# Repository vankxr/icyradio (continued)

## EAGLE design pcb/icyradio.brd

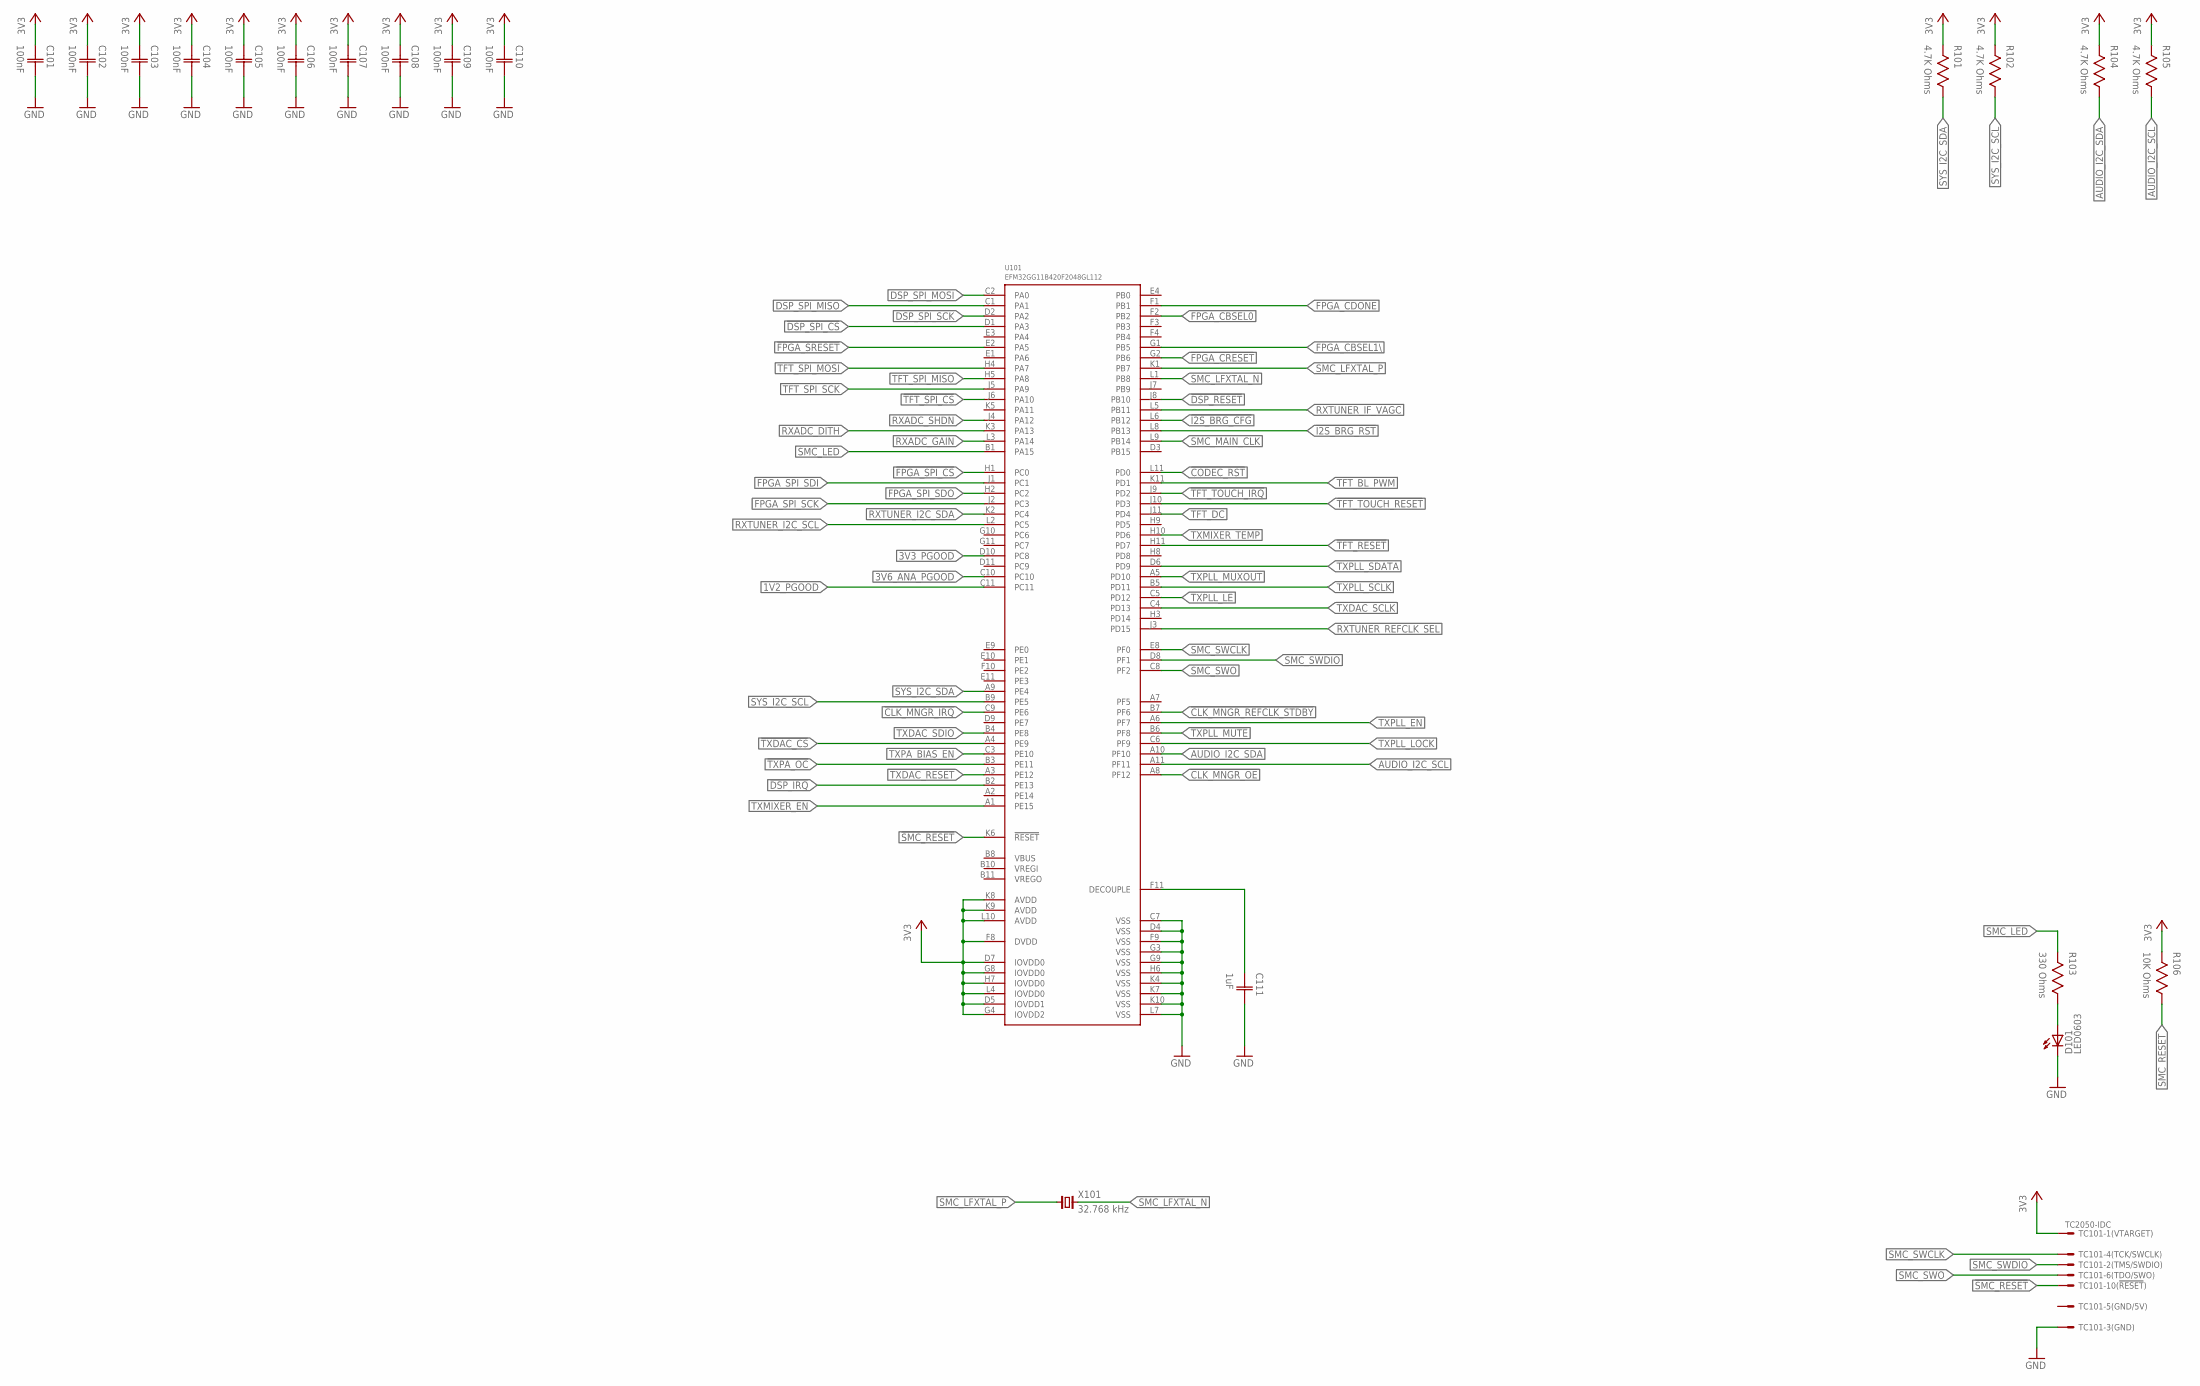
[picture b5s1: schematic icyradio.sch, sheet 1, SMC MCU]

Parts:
C101, C102, C103, C104, C105, C106, C107, C108, C109, C110: 100nF; CAP0603
C111: 1uF; CAP0603
D101: LED0603; 0603
R101, R102, R104, R105: 4.7K Ohms; RES0603
R103: 330 Ohms; RES0603
R106: 10K Ohms; RES0603
TC101: TC2050-IDC
U101: EFM32GG11B420F2048GL112; BGA112
X101: 32.768 kHz; 2-SMD-3215

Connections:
1V2_PGOOD: U101.C11; also elsewhere on the board
3V3: C101.1 (C1), C102.1 (C1), C103.1 (C1), C104.1 (C1), C105.1 (C1), C106.1 (C1), C107.1 (C1), C108.1 (C1), C109.1 (C1), C110.1 (C1), R101.2, R102.2, R104.2, R105.2, R106.2, TC101.1, U101.D5 (IOVDD1), U101.D7 (IOVDD0), U101.F8 (DVDD), U101.G4 (IOVDD2), U101.G8 (IOVDD0), U101.H7 (IOVDD0), U101.K8 (AVDD), U101.K9 (AVDD), U101.L4 (IOVDD0), U101.L10 (AVDD); also elsewhere on the board
3V3_PGOOD: U101.D10 (PC8); also elsewhere on the board
3V6_ANA_PGOOD: U101.C10; also elsewhere on the board
!CLK_MNGR_IRQ: U101.C9 (PE6); also elsewhere on the board
!CLK_MNGR_OE: U101.A8 (PF12); also elsewhere on the board
!CLK_MNGR_REFCLK_STDBY: U101.B7 (PF6); also elsewhere on the board
!CODEC_RST: U101.L11 (PD0); also elsewhere on the board
!DSP_IRQ: U101.B2 (PE13); also elsewhere on the board
!DSP_RESET: U101.J8 (PB10); also elsewhere on the board
!DSP_SPI_CS: U101.D1 (PA3); also elsewhere on the board
!FPGA_CRESET: U101.G2 (PB6); also elsewhere on the board
!FPGA_SPI_CS: U101.H1 (PC0); also elsewhere on the board
!FPGA_SRESET: U101.E2 (PA5); also elsewhere on the board
!I2S_BRG_CFG: U101.L6 (PB12); also elsewhere on the board
!I2S_BRG_RST: U101.L8 (PB13); also elsewhere on the board
!SMC_RESET: R106.1, TC101.10, U101.K6 (!RESET)
!TFT_RESET: U101.H11 (PD7); also elsewhere on the board
!TFT_SPI_CS: U101.J6 (PA10); also elsewhere on the board
!TFT_TOUCH_IRQ: U101.J9 (PD2); also elsewhere on the board
!TFT_TOUCH_RESET: U101.J10 (PD3); also elsewhere on the board
!TXDAC_CS: U101.A4 (PE9); also elsewhere on the board
!TXPA_OC: U101.B3 (PE11); also elsewhere on the board
!TXPLL_MUTE: U101.B6 (PF8); also elsewhere on the board
AUDIO_I2C_SCL: R105.1, U101.A11 (PF11); also elsewhere on the board
AUDIO_I2C_SDA: R104.1, U101.A10 (PF10); also elsewhere on the board
DSP_SPI_MISO: U101.C1 (PA1); also elsewhere on the board
DSP_SPI_MOSI: U101.C2 (PA0); also elsewhere on the board
DSP_SPI_SCK: U101.D2 (PA2); also elsewhere on the board
FPGA_CBSEL0: U101.F2 (PB2); also elsewhere on the board
FPGA_CBSEL1\: U101.G1 (PB5); also elsewhere on the board
FPGA_CDONE: U101.F1 (PB1); also elsewhere on the board
FPGA_SPI_SCK: U101.J2 (PC3); also elsewhere on the board
FPGA_SPI_SDI: U101.J1 (PC1); also elsewhere on the board
FPGA_SPI_SDO: U101.H2 (PC2); also elsewhere on the board
GND: C101.2 (C2), C102.2 (C2), C103.2 (C2), C104.2 (C2), C105.2 (C2), C106.2 (C2), C107.2 (C2), C108.2 (C2), C109.2 (C2), C110.2 (C2), C111.2 (C2), D101.1 (C), TC101.3, U101.C7 (VSS), U101.D4 (VSS), U101.F9 (VSS), U101.G3 (VSS), U101.G9 (VSS), U101.H6 (VSS), U101.K4 (VSS), U101.K7 (VSS), U101.K10 (VSS), U101.L7 (VSS); also elsewhere on the board
unnamed: D101.2 (A), R103.1
RXADC_DITH: U101.K3 (PA13); also elsewhere on the board
RXADC_GAIN: U101.L3 (PA14); also elsewhere on the board
RXADC_SHDN: U101.J4 (PA12); also elsewhere on the board
RXTUNER_I2C_SCL: U101.L2 (PC5); also elsewhere on the board
RXTUNER_I2C_SDA: U101.K2 (PC4); also elsewhere on the board
RXTUNER_IF_VAGC: U101.L5 (PB11); also elsewhere on the board
RXTUNER_REFCLK_SEL: U101.J3 (PD15); also elsewhere on the board
SMC_LED: R103.2, U101.B1 (PA15)
SMC_LFXTAL_N: U101.L1 (PB8), X101.2
SMC_LFXTAL_P: U101.K1 (PB7), X101.1
SMC_MAIN_CLK: U101.L9 (PB14); also elsewhere on the board
SMC_SWCLK: TC101.4, U101.E8 (PF0)
SMC_SWDIO: TC101.2, U101.D8 (PF1)
SMC_SWO: TC101.6, U101.C8 (PF2)
SMC_VCORE: C111.1 (C1), U101.F11 (DECOUPLE)
SYS_I2C_SCL: R102.1, U101.B9 (PE5); also elsewhere on the board
SYS_I2C_SDA: R101.1, U101.A9 (PE4); also elsewhere on the board
TFT_BL_PWM: U101.K11 (PD1); also elsewhere on the board
TFT_DC: U101.J11 (PD4); also elsewhere on the board
TFT_SPI_MISO: U101.H5 (PA8); also elsewhere on the board
TFT_SPI_MOSI: U101.H4 (PA7); also elsewhere on the board
TFT_SPI_SCK: U101.J5 (PA9); also elsewhere on the board
TXDAC_RESET: U101.A3 (PE12); also elsewhere on the board
TXDAC_SCLK: U101.C4 (PD13); also elsewhere on the board
TXDAC_SDIO: U101.B4 (PE8); also elsewhere on the board
TXMIXER_EN: U101.A1 (PE15); also elsewhere on the board
TXMIXER_TEMP: U101.H10 (PD6); also elsewhere on the board
TXPA_BIAS_EN: U101.C3 (PE10); also elsewhere on the board
TXPLL_EN: U101.A6 (PF7); also elsewhere on the board
TXPLL_LE: U101.C5 (PD12); also elsewhere on the board
TXPLL_LOCK: U101.C6 (PF9); also elsewhere on the board
TXPLL_MUXOUT: U101.A5 (PD10); also elsewhere on the board
TXPLL_SCLK: U101.B5 (PD11); also elsewhere on the board
TXPLL_SDATA: U101.D6 (PD9); also elsewhere on the board

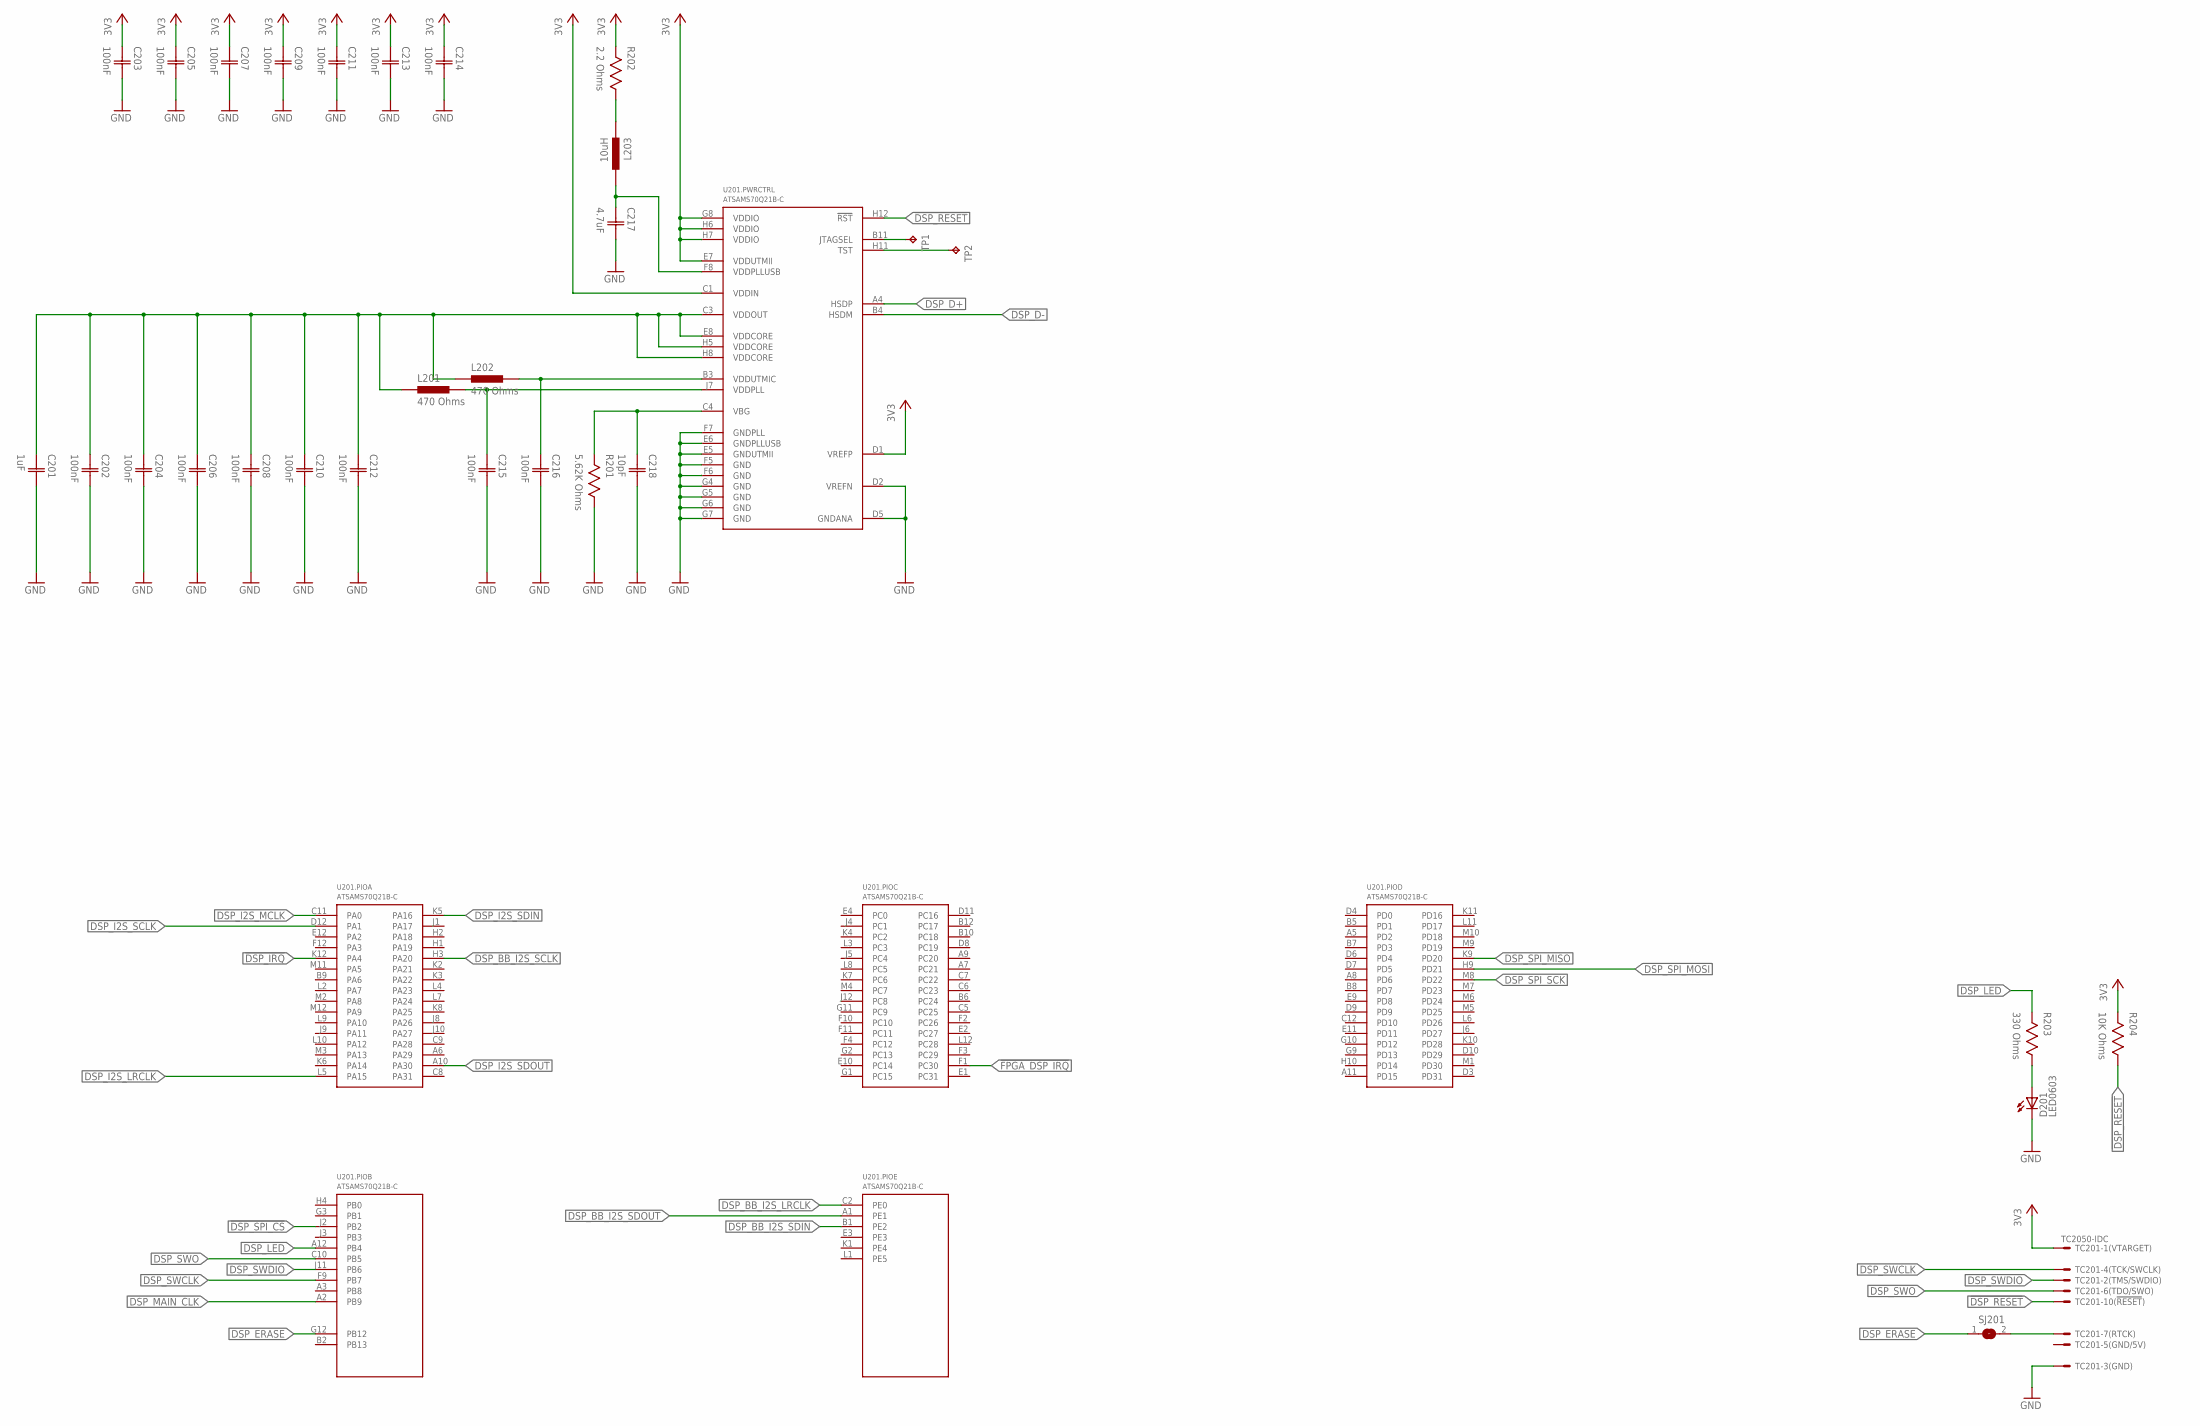
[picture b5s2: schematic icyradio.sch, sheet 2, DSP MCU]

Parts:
C201: 1uF; CAP0603
C202, C203, C204, C205, C206, C207, C208, C209, C210, C211, C212, C213, C214, C215, C216: 100nF; CAP0603
C217: 4.7uF; CAP0603
C218: 10pF; CAP0603
D201: LED0603; 0603
L201, L202: 470 Ohms; IND0603
L203: 10uH; IND0603
R201: 5.62K Ohms; RES0603
R202: 2.2 Ohms; RES0603
R203: 330 Ohms; RES0603
R204: 10K Ohms; RES0603
SJ201: SJS; SJ_S
TC201: TC2050-IDC
TP1, TP2: TESTPOINT-0.7MM; PAD0.7MM
U201: ATSAMS70Q21B-C; LFBGA144

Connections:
3V3: C203.1 (C1), C205.1 (C1), C207.1 (C1), C209.1 (C1), C211.1 (C1), C213.1 (C1), C214.1 (C1), R202.2, R204.2, TC201.1, U201.C1 (VDDIN), U201.D1 (VREFP), U201.E7 (VDDUTMII), U201.G8 (VDDIO), U201.H6 (VDDIO), U201.H7 (VDDIO); also elsewhere on the board
!DSP_IRQ: U201.K12 (PA4); also elsewhere on the board
!DSP_RESET: R204.1, TC201.10, U201.H12 (!RST); also elsewhere on the board
!DSP_SPI_CS: U201.J2 (PB2); also elsewhere on the board
!FPGA_DSP_IRQ: U201.F1 (PC30); also elsewhere on the board
DSP_BB_I2S_LRCLK: U201.C2 (PE0); also elsewhere on the board
DSP_BB_I2S_SCLK: U201.H3 (PA20); also elsewhere on the board
DSP_BB_I2S_SDIN: U201.B1 (PE2); also elsewhere on the board
DSP_BB_I2S_SDOUT: U201.A1 (PE1); also elsewhere on the board
DSP_D+: U201.A4 (HSDP); also elsewhere on the board
DSP_D-: U201.B4 (HSDM); also elsewhere on the board
DSP_ERASE: SJ201.1, U201.G12 (PB12)
DSP_I2S_LRCLK: U201.L5 (PA15); also elsewhere on the board
DSP_I2S_MCLK: U201.C11 (PA0); also elsewhere on the board
DSP_I2S_SCLK: U201.D12 (PA1); also elsewhere on the board
DSP_I2S_SDIN: U201.K5 (PA16); also elsewhere on the board
DSP_I2S_SDOUT: U201.A10 (PA30); also elsewhere on the board
DSP_JTAGSEL: TP1.TP, U201.B11 (JTAGSEL)
DSP_LED: R203.2, U201.A12 (PB4)
DSP_MAIN_CLK: U201.A2 (PB9); also elsewhere on the board
DSP_SPI_MISO: U201.K9 (PD20); also elsewhere on the board
DSP_SPI_MOSI: U201.H9 (PD21); also elsewhere on the board
DSP_SPI_SCK: U201.M8 (PD22); also elsewhere on the board
DSP_SWCLK: TC201.4, U201.F9 (PB7)
DSP_SWDIO: TC201.2, U201.J11 (PB6)
DSP_SWO: TC201.6, U201.C10 (PB5)
DSP_TST: TP2.TP, U201.H11 (TST)
DSP_VDDOUT: C201.1 (C1), C202.1 (C1), C204.1 (C1), C206.1 (C1), C208.1 (C1), C210.1 (C1), C212.1 (C1), L201.1, L202.1, U201.C3 (VDDOUT), U201.E8 (VDDCORE), U201.H5 (VDDCORE), U201.H8 (VDDCORE)
DSP_VDDPLLUSB: C217.1 (C1), L203.2, U201.F8 (VDDPLLUSB)
GND: C201.2 (C2), C202.2 (C2), C203.2 (C2), C204.2 (C2), C205.2 (C2), C206.2 (C2), C207.2 (C2), C208.2 (C2), C209.2 (C2), C210.2 (C2), C211.2 (C2), C212.2 (C2), C213.2 (C2), C214.2 (C2), C215.2 (C2), C216.2 (C2), C217.2 (C2), C218.2 (C2), D201.1 (C), R201.1, TC201.3, U201.D2 (VREFN), U201.D5 (GNDANA), U201.E5 (GNDUTMII), U201.E6 (GNDPLLUSB), U201.F5 (GND), U201.F6 (GND), U201.F7 (GNDPLL), U201.G4 (GND), U201.G5 (GND), U201.G6 (GND), U201.G7 (GND); also elsewhere on the board
unnamed: L203.1, R202.1
unnamed: C218.1 (C1), R201.2, U201.C4 (VBG)
unnamed: C215.1 (C1), L201.2, U201.J7 (VDDPLL)
unnamed: C216.1 (C1), L202.2, U201.B3 (VDDUTMIC)
unnamed: SJ201.2, TC201.7
unnamed: D201.2 (A), R203.1

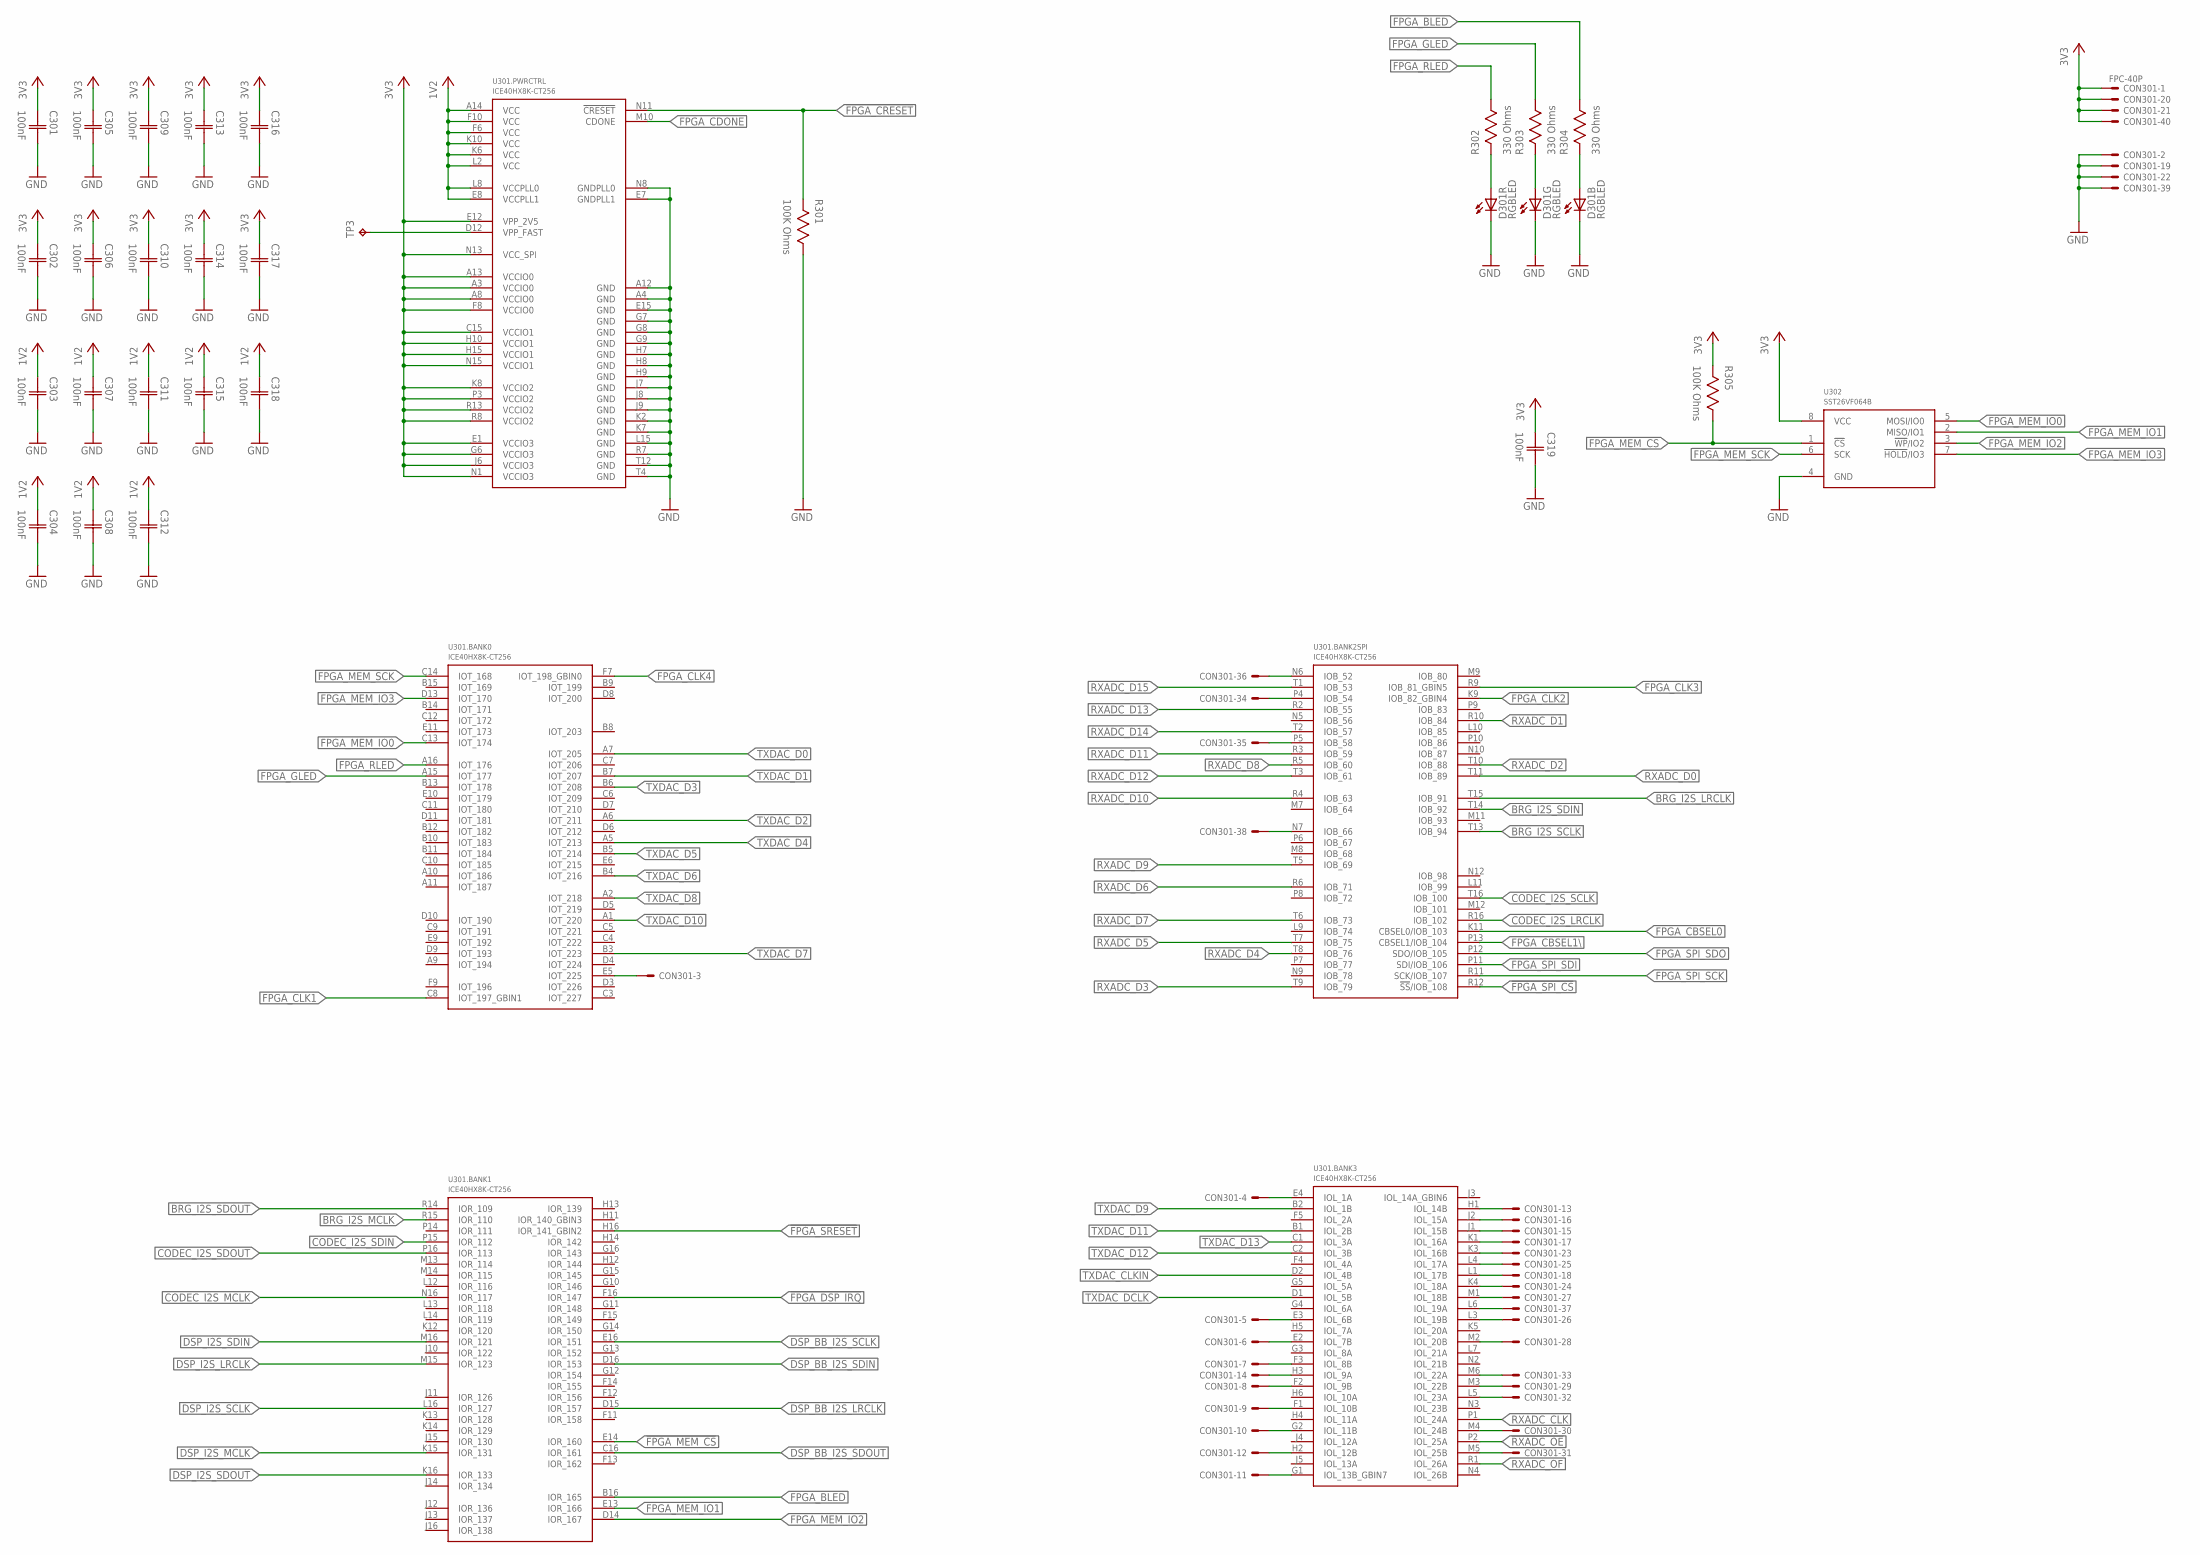
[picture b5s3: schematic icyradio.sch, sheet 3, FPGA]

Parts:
C301, C302, C303, C304, C305, C306, C307, C308, C309, C310, C311, C312, C313, C314, C315, C316, C317, C318, C319: 100nF; CAP0603
CON301: FPC-40P
D301: RGBLED; 5050
R301, R305: 100K Ohms; RES0603
R302, R303, R304: 330 Ohms; RES0603
TP3: TESTPOINT-0.7MM; PAD0.7MM
U301: ICE40HX8K-CT256; CABGA256
U302: SST26VF064B; WSOIC8

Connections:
1V2: C303.1 (C1), C304.1 (C1), C307.1 (C1), C308.1 (C1), C311.1 (C1), C312.1 (C1), C315.1 (C1), C318.1 (C1), U301.A14 (VCC), U301.E8 (VCCPLL1), U301.F6 (VCC), U301.F10 (VCC), U301.K6 (VCC), U301.K10 (VCC), U301.L2 (VCC), U301.L8 (VCCPLL0); also elsewhere on the board
3V3: C301.1 (C1), C302.1 (C1), C305.1 (C1), C306.1 (C1), C309.1 (C1), C310.1 (C1), C313.1 (C1), C314.1 (C1), C316.1 (C1), C317.1 (C1), C319.1 (C1), CON301.1, CON301.20, CON301.21, CON301.40, R305.2, U301.A3 (VCCIO0), U301.A8 (VCCIO0), U301.A13 (VCCIO0), U301.C15 (VCCIO1), U301.E1 (VCCIO3), U301.E12 (VPP_2V5), U301.F8 (VCCIO0), U301.G6 (VCCIO3), U301.H10 (VCCIO1), U301.H15 (VCCIO1), U301.J6 (VCCIO3), U301.K8 (VCCIO2), U301.N1 (VCCIO3), U301.N13 (VCC_SPI), U301.N15 (VCCIO1), U301.P3 (VCCIO2), U301.R8 (VCCIO2), U301.R13 (VCCIO2), U302.8 (VCC); also elsewhere on the board
!FPGA_CRESET: R301.2, U301.N11 (!CRESET); also elsewhere on the board
!FPGA_DSP_IRQ: U301.F16 (IOR_147); also elsewhere on the board
!FPGA_MEM_CS: R305.1, U301.E14 (IOR_160), U302.1 (!CS!)
!FPGA_SPI_CS: U301.R12 (!SS!/IOB_108); also elsewhere on the board
!FPGA_SRESET: U301.H16 (IOR_141_GBIN2); also elsewhere on the board
!RXADC_OE: U301.P2 (IOL_25A); also elsewhere on the board
BRG_I2S_LRCLK: U301.T15 (IOB_91); also elsewhere on the board
BRG_I2S_MCLK: U301.R15 (IOR_110); also elsewhere on the board
BRG_I2S_SCLK: U301.T13 (IOB_94); also elsewhere on the board
BRG_I2S_SDIN: U301.T14 (IOB_92); also elsewhere on the board
BRG_I2S_SDOUT: U301.R14 (IOR_109); also elsewhere on the board
CODEC_I2S_LRCLK: U301.R16 (IOB_102); also elsewhere on the board
CODEC_I2S_MCLK: U301.N16 (IOR_117); also elsewhere on the board
CODEC_I2S_SCLK: U301.T16 (IOB_100); also elsewhere on the board
CODEC_I2S_SDIN: U301.P15 (IOR_112); also elsewhere on the board
CODEC_I2S_SDOUT: U301.P16 (IOR_113); also elsewhere on the board
DSP_BB_I2S_LRCLK: U301.D15 (IOR_157); also elsewhere on the board
DSP_BB_I2S_SCLK: U301.E16 (IOR_151); also elsewhere on the board
DSP_BB_I2S_SDIN: U301.D16 (IOR_153); also elsewhere on the board
DSP_BB_I2S_SDOUT: U301.C16 (IOR_161); also elsewhere on the board
DSP_I2S_LRCLK: U301.M15 (IOR_123); also elsewhere on the board
DSP_I2S_MCLK: U301.K15 (IOR_131); also elsewhere on the board
DSP_I2S_SCLK: U301.L16 (IOR_127); also elsewhere on the board
DSP_I2S_SDIN: U301.M16 (IOR_121); also elsewhere on the board
DSP_I2S_SDOUT: U301.K16 (IOR_133); also elsewhere on the board
EXP_IO0: CON301.3, U301.E5 (IOT_225)
EXP_IO1: CON301.4, U301.E4 (IOL_1A)
EXP_IO2: CON301.5, U301.E3 (IOL_6B)
EXP_IO3: CON301.6, U301.E2 (IOL_7B)
EXP_IO4: CON301.7, U301.F3 (IOL_8B)
EXP_IO5: CON301.8, U301.F2 (IOL_9B)
EXP_IO6: CON301.9, U301.F1 (IOL_10B)
EXP_IO7: CON301.10, U301.G2 (IOL_11B)
EXP_IO8: CON301.11, U301.G1 (IOL_13B_GBIN7)
EXP_IO9: CON301.12, U301.H2 (IOL_12B)
EXP_IO10: CON301.13, U301.H1 (IOL_14B)
EXP_IO11: CON301.14, U301.H3 (IOL_9A)
EXP_IO12: CON301.15, U301.J1 (IOL_15B)
EXP_IO13: CON301.16, U301.J2 (IOL_15A)
EXP_IO14: CON301.17, U301.K1 (IOL_16A)
EXP_IO15: CON301.18, U301.L1 (IOL_17B)
EXP_IO16: CON301.23, U301.K3 (IOL_16B)
EXP_IO17: CON301.24, U301.K4 (IOL_18A)
EXP_IO18: CON301.25, U301.L4 (IOL_17A)
EXP_IO19: CON301.26, U301.L3 (IOL_19B)
EXP_IO20: CON301.27, U301.M1 (IOL_18B)
EXP_IO21: CON301.28, U301.M2 (IOL_20B)
EXP_IO22: CON301.29, U301.M3 (IOL_22B)
EXP_IO23: CON301.30, U301.M4 (IOL_24B)
EXP_IO24: CON301.31, U301.M5 (IOL_25B)
EXP_IO25: CON301.32, U301.L5 (IOL_23A)
EXP_IO26: CON301.33, U301.M6 (IOL_22A)
EXP_IO27: CON301.34, U301.P4 (IOB_54)
EXP_IO28: CON301.35, U301.P5 (IOB_58)
EXP_IO29: CON301.36, U301.N6 (IOB_52)
EXP_IO30: CON301.37, U301.L6 (IOL_19A)
EXP_IO31: CON301.38, U301.N7 (IOB_66)
FPGA_BLED: R304.1, U301.B16 (IOR_165)
FPGA_CBSEL0: U301.K11 (CBSEL0/IOB_103); also elsewhere on the board
FPGA_CBSEL1\: U301.P13 (CBSEL1/IOB_104); also elsewhere on the board
FPGA_CDONE: U301.M10 (CDONE); also elsewhere on the board
FPGA_CLK1: U301.C8 (IOT_197_GBIN1); also elsewhere on the board
FPGA_CLK2: U301.K9 (IOB_82_GBIN4); also elsewhere on the board
FPGA_CLK3: U301.R9 (IOB_81_GBIN5); also elsewhere on the board
FPGA_CLK4: U301.F7 (IOT_198_GBIN0); also elsewhere on the board
FPGA_GLED: R303.1, U301.A15 (IOT_177)
FPGA_MEM_IO0: U301.C13 (IOT_174), U302.5 (MOSI/IO0)
FPGA_MEM_IO1: U301.E13 (IOR_166), U302.2 (MISO/IO1)
FPGA_MEM_IO2: U301.D14 (IOR_167), U302.3 (!WP!/IO2)
FPGA_MEM_IO3: U301.D13 (IOT_170), U302.7 (!HOLD!/IO3)
FPGA_MEM_SCK: U301.C14 (IOT_168), U302.6 (SCK)
FPGA_RLED: R302.1, U301.A16 (IOT_176)
FPGA_SPI_SCK: U301.R11 (SCK/IOB_107); also elsewhere on the board
FPGA_SPI_SDI: U301.P11 (SDI/IOB_106); also elsewhere on the board
FPGA_SPI_SDO: U301.P12 (SDO/IOB_105); also elsewhere on the board
FPGA_VPP_FAST: TP3.TP, U301.D12 (VPP_FAST)
GND: C301.2 (C2), C302.2 (C2), C303.2 (C2), C304.2 (C2), C305.2 (C2), C306.2 (C2), C307.2 (C2), C308.2 (C2), C309.2 (C2), C310.2 (C2), C311.2 (C2), C312.2 (C2), C313.2 (C2), C314.2 (C2), C315.2 (C2), C316.2 (C2), C317.2 (C2), C318.2 (C2), C319.2 (C2), CON301.2, CON301.19, CON301.22, CON301.39, D301.4 (C), D301.5 (C), D301.6 (C), R301.1, U301.A4 (GND), U301.A12 (GND), U301.E7 (GNDPLL1), U301.E15 (GND), U301.G7 (GND), U301.G8 (GND), U301.G9 (GND), U301.H7 (GND), U301.H8 (GND), U301.H9 (GND), U301.J7 (GND), U301.J8 (GND), U301.J9 (GND), U301.K2 (GND), U301.K7 (GND), U301.L15 (GND), U301.N8 (GNDPLL0), U301.R7 (GND), U301.T4 (GND), U301.T12 (GND), U302.4 (GND); also elsewhere on the board
unnamed: D301.2 (A), R302.2
unnamed: D301.1 (A), R303.2
unnamed: D301.3 (A), R304.2
RXADC_CLK: U301.P1 (IOL_24A); also elsewhere on the board
RXADC_D0: U301.T11 (IOB_89); also elsewhere on the board
RXADC_D1: U301.R10 (IOB_84); also elsewhere on the board
RXADC_D2: U301.T10 (IOB_88); also elsewhere on the board
RXADC_D3: U301.T9 (IOB_79); also elsewhere on the board
RXADC_D4: U301.T8 (IOB_76); also elsewhere on the board
RXADC_D5: U301.T7 (IOB_75); also elsewhere on the board
RXADC_D6: U301.R6 (IOB_71); also elsewhere on the board
RXADC_D7: U301.T6 (IOB_73); also elsewhere on the board
RXADC_D8: U301.R5 (IOB_60); also elsewhere on the board
RXADC_D9: U301.T5 (IOB_69); also elsewhere on the board
RXADC_D10: U301.R4 (IOB_63); also elsewhere on the board
RXADC_D11: U301.R3 (IOB_59); also elsewhere on the board
RXADC_D12: U301.T3 (IOB_61); also elsewhere on the board
RXADC_D13: U301.R2 (IOB_55); also elsewhere on the board
RXADC_D14: U301.T2 (IOB_57); also elsewhere on the board
RXADC_D15: U301.T1 (IOB_53); also elsewhere on the board
RXADC_OF: U301.R1 (IOL_26A); also elsewhere on the board
TXDAC_CLKIN: U301.D2 (IOL_4B); also elsewhere on the board
TXDAC_D0: U301.A7 (IOT_205); also elsewhere on the board
TXDAC_D1: U301.B7 (IOT_207); also elsewhere on the board
TXDAC_D2: U301.A6 (IOT_211); also elsewhere on the board
TXDAC_D3: U301.B6 (IOT_208); also elsewhere on the board
TXDAC_D4: U301.A5 (IOT_213); also elsewhere on the board
TXDAC_D5: U301.B5 (IOT_214); also elsewhere on the board
TXDAC_D6: U301.B4 (IOT_216); also elsewhere on the board
TXDAC_D7: U301.B3 (IOT_223); also elsewhere on the board
TXDAC_D8: U301.A2 (IOT_218); also elsewhere on the board
TXDAC_D9: U301.B2 (IOL_1B); also elsewhere on the board
TXDAC_D10: U301.A1 (IOT_220); also elsewhere on the board
TXDAC_D11: U301.B1 (IOL_2B); also elsewhere on the board
TXDAC_D12: U301.C2 (IOL_3B); also elsewhere on the board
TXDAC_D13: U301.C1 (IOL_3A); also elsewhere on the board
TXDAC_DCLK: U301.D1 (IOL_5B); also elsewhere on the board
